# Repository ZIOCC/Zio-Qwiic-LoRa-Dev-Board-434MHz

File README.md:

# Zio Qwiic LoRa Dev Board 443MHz

> This product can be available for purchase [here](https://www.smart-prototyping.com/Zio-Qwiic-LoRa-Dev-Board-443MHz).

#### Description

We know how complicated it is to connect LoRa module, so we make your ‘connecting’ life easier. We created an Arduino IDE compatible board which combines LoRa module + ATMEGA32U4-AU. Simply use two boards, one as a transmitter and another one as a receiver, and the LoRa setup is complete!

There are two Qwiic connectors on board, so you can add more Qwiic modules within seconds without soldering and jumper wire connection. 

The Main IC ATMEGA32U4-AU has almost the same performance as ATmega328, with built-in USB so not only does it have a USB-to-Serial program and debug capability built in with no need for an FTDI-like chip, it can also act like a mouse, keyboard, USB MIDI device, etc.
You can download the driver for ATMEGA32U4-AU [here](https://github.com/adafruit/Adafruit_Windows_Drivers/releases/download/1.2/adafruit_drivers.exe). Alternatively, you can check out the installation guide [here](https://learn.adafruit.com/adafruit-arduino-ide-setup/windows-driver-installation).

The LoRa module on board is based on SX1278 and works on a 433MHz frequency. It can work as master model or slave model. With a spring antenna, the communication distance can reach up to 10 KM in open field. It is a perfect solution for building projects that need to cross a big area. We offer two kinds of LoRa modules on board (optional), the Ra-01 with spring antenna and Ra-02 with IPX antenna. 

The onboard antenna is good enough for you to test function, if you need to implement it for real projects, please solder the antenna to get the best spreading distance.

> If you are looking for the Lora Module instead, you can find it [here](https://www.smart-prototyping.com/index.php?route=product/search&search=lora)

#### Specification

* Program Memory Size (KB): 32
* CPU Speed (MIPS/DMIPS): 16
* SRAM Bytes: 2,560
* Data EEPROM/HEF (bytes): 1024
* Wireless Standard: 433MHz
* Frequency range: 420 - 450MHz

#### Links

* [PCB source file and Gerber file](https://github.com/ZIOCC/Zio-Qwiic-LoRa-Dev-Board-434MHz)
* [Demo code](https://github.com/ZIOCC/Zio-Qwiic-LoRa-Dev-Board-434MHz/tree/master/arduino-LoRa-master)
* [ATMEGA32U4-AU datasheet](http://ww1.microchip.com/downloads/en/DeviceDoc/Atmel-7766-8-bit-AVR-ATmega16U4-32U4_Datasheet.pdf)
* [Arduino IDE Bootloader](https://github.com/adafruit/Adafruit_Windows_Drivers/releases/download/1.2/adafruit_drivers.exe)

###### About Zio
> Zio is a new line of open sourced, compact, and grid layout boards, fully integrated for Arduino and Qwiic ecosystem. Designed ideally for wearables, robotics, small-space limitations or other on the go projects. Check out other awesome Zio products [here](https://www.smart-prototyping.com/Zio).

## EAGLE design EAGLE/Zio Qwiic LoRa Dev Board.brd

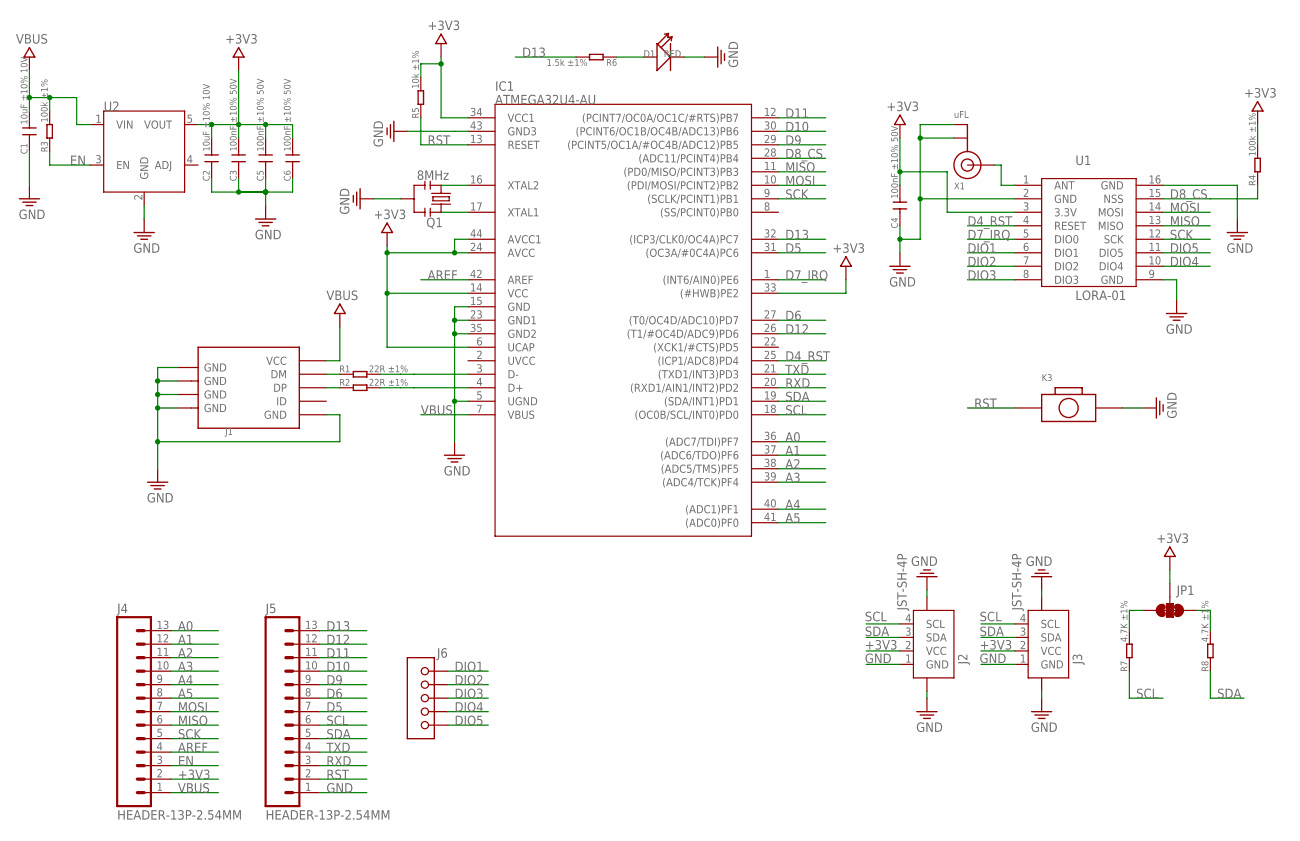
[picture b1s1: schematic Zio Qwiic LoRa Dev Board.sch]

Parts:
C1, C2: 10uF ±10% 10V; C0603
C3, C4, C5, C6: 100nF ±10% 50V; C0603
D1: RED; LED-0603
IC1: ATMEGA32U4-AU; TQFP44
J1: USB-MICROE; MICRO-SMD
J2, J3: JST-SH-4P; JST-SH-4P-90
J4, J5: HEADER-13P-2.54MM; 13P-SCREW-2.54
J6: HEADER-5P-2.54; 5P-2.54
JP1: SMT-JUMPER_3_2-NC_TRACE
K3: BOTTON-2PSKRKAEE020; SKRKAEE020
Q1: 8MHz; RESONATOR-SMD
R1, R2: 22R ±1%; R0603
R3, R4: 100k ±1%; R0603
R5: 10k ±1%; R0603
R6: 1.5k ±1%; R0603
R7, R8: 4.7K ±1%; R0603
U1: LORA-01
U2: AP2112; SOT23-5
X1: uFL; U.FL

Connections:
+3V3: C2.2, C3.2, C4.2, C5.2, C6.2, IC1.6 (UCAP), IC1.14 (VCC), IC1.24 (AVCC), IC1.33 ((#HWB)PE2), IC1.34 (VCC1), IC1.44 (AVCC1), J2.2 (VCC), J3.2 (VCC), J4.2, JP1.2, R4.2, R5.2, U1.3 (3.3V), U2.5 (VOUT)
A0: IC1.36 ((ADC7/TDI)PF7), J4.13
A1: IC1.37 ((ADC6/TDO)PF6), J4.12
A2: IC1.38 ((ADC5/TMS)PF5), J4.11
A3: IC1.39 ((ADC4/TCK)PF4), J4.10
A4: IC1.40 ((ADC1)PF1), J4.9
A5: IC1.41 ((ADC0)PF0), J4.8
AREF: IC1.42 (AREF), J4.4
D4_RST: IC1.25 ((ICP1/ADC8)PD4), U1.4 (RESET)
D5: IC1.31 ((OC3A/#0C4A)PC6), J5.7
D6: IC1.27 ((T0/OC4D/ADC10)PD7), J5.8
D7_IRQ: IC1.1 ((INT6/AIN0)PE6), U1.5 (DIO0)
D8_CS: IC1.28 ((ADC11/PCINT4)PB4), R4.1, U1.15 (NSS)
D9: IC1.29 ((PCINT5/OC1A/#OC4B/ADC12)PB5), J5.9
D10: IC1.30 ((PCINT6/OC1B/OC4B/ADC13)PB6), J5.10
D11: IC1.12 ((PCINT7/OC0A/OC1C/#RTS)PB7), J5.11
D12: IC1.26 ((T1/#OC4D/ADC9)PD6), J5.12
D13: IC1.32 ((ICP3/CLK0/OC4A)PC7), J5.13, R6.2
DIO1: J6.1, U1.6 (DIO1)
DIO2: J6.2, U1.7 (DIO2)
DIO3: J6.3, U1.8 (DIO3)
DIO4: J6.4, U1.10 (DIO4)
DIO5: J6.5, U1.11 (DIO5)
EN: J4.3, R3.1, U2.3 (EN)
GND: C1.1, C2.1, C3.1, C4.1, C5.1, C6.1, D1.-, IC1.5 (UGND), IC1.15 (GND), IC1.23 (GND1), IC1.35 (GND2), IC1.43 (GND3), J1.GND, J1.S1 (GND), J1.S1@1 (GND), J1.S1@2 (GND), J1.S2 (GND), J1.S2@1 (GND), J1.S2@2 (GND), J1.S3 (GND), J1.S3@1 (GND), J1.S3@2 (GND), J1.S4 (GND), J1.S4@1 (GND), J1.S4@2 (GND), J1.S5 (GND), J1.S6 (GND), J2.1 (GND), J2.5, J2.6, J3.1 (GND), J3.5, J3.6, J5.1, K3.2, Q1.2, U1.2 (GND), U1.9 (GND), U1.16 (GND), U2.2 (GND), X1.1 (GND), X1.2 (GND)
MISO: IC1.11 ((PD0/MISO/PCINT3)PB3), J4.6, U1.13 (MISO)
MOSI: IC1.10 ((PDI/MOSI/PCINT2)PB2), J4.7, U1.14 (MOSI)
unnamed: J1.D- (DM), R1.1
unnamed: J1.D+ (DP), R2.1
unnamed: IC1.4 (D+), R2.2
unnamed: IC1.3 (D-), R1.2
unnamed: IC1.16 (XTAL2), Q1.3
unnamed: D1.+, R6.1
unnamed: IC1.17 (XTAL1), Q1.1
unnamed: U1.1 (ANT), X1.3 (SIGNAL)
unnamed: JP1.3, R7.2
unnamed: JP1.1, R8.2
RST: IC1.13 (RESET), J5.2, K3.1, R5.1
RXD: IC1.20 ((RXD1/AIN1/INT2)PD2), J5.3
SCK: IC1.9 ((SCLK/PCINT1)PB1), J4.5, U1.12 (SCK)
SCL: IC1.18 ((OC0B/SCL/INT0)PD0), J2.4 (SCL), J3.4 (SCL), J5.6, R7.1
SDA: IC1.19 ((SDA/INT1)PD1), J2.3 (SDA), J3.3 (SDA), J5.5, R8.1
TXD: IC1.21 ((TXD1/INT3)PD3), J5.4
VBUS: C1.2, IC1.7 (VBUS), J1.VBUS (VCC), J4.1, R3.2, U2.1 (VIN)

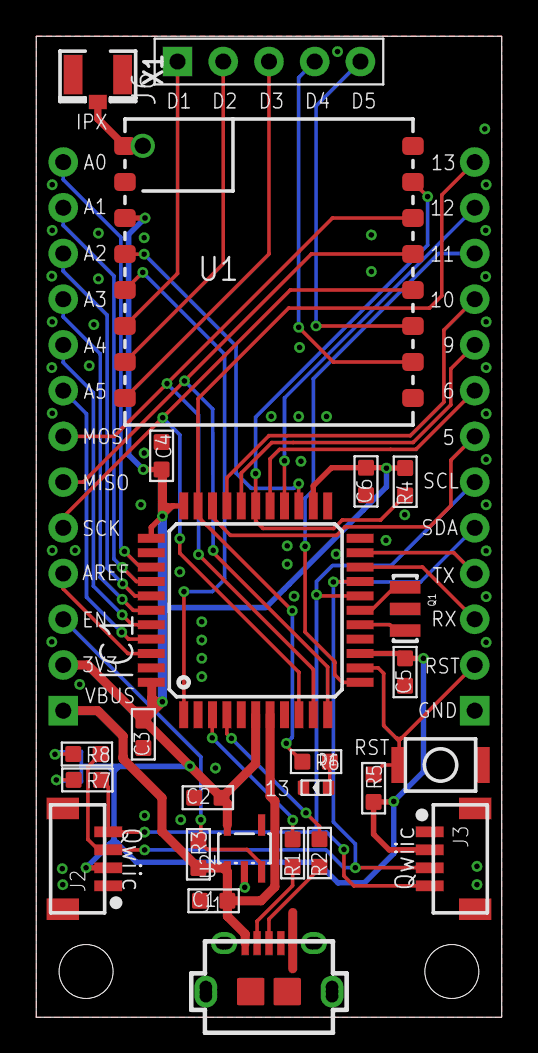
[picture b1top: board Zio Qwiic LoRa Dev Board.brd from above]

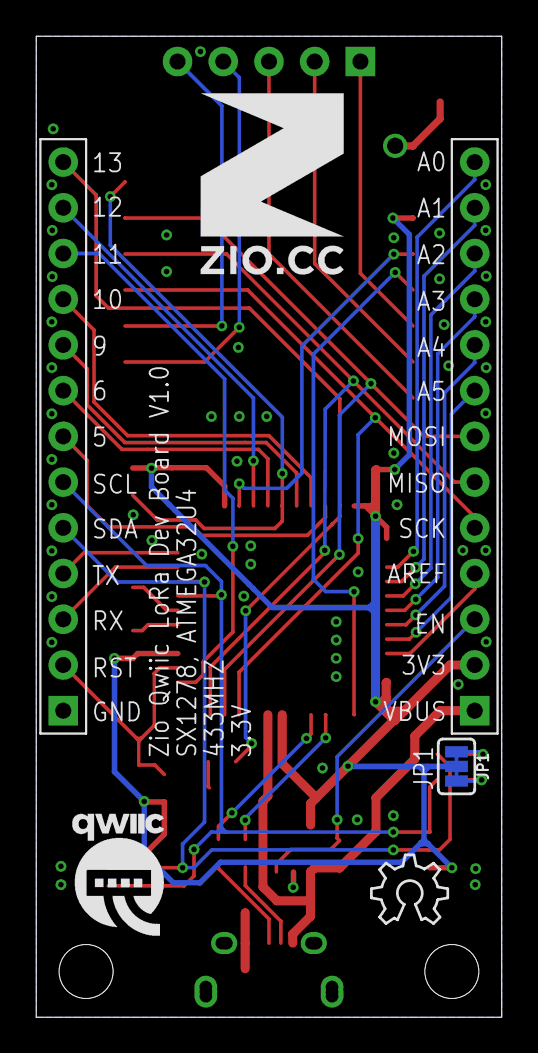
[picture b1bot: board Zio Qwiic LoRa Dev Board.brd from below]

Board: 2 copper layers, 25.9 x 54.5 mm, 31 parts (6 on the bottom side), 44 nets.

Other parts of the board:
U$10: 10MM
U$11: QWIIC-LOGO-MEDIUM
U$12: OSHW_6X150_NOTEXT

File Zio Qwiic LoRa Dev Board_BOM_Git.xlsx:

| BOM quantity |  |  | Zio Qwiic LoRa Dev Board | V 1.0 |  |  |  |  | Harry | 2018.8.31
 | Part Identification |  |  |  |  |  |  |  | Customer Information |  | Quantity
# | Part ID / Reference | Manufacturer | Part / Order Number | Description | Value | Package | THT (y/n) | Pins / Pads | Source/Link/ Datasheet/Note | Source / Target Price | Quantity per BOM
1 | C1, C2 |  |  |  | 10uF ±10% 10V | C0603 | n | 2 |  |  | 2
2 | C3, C4, C5, C6 |  |  |  | 100nF ±10% 50V | C0603 | n | 2 |  |  | 4
3 | D1 |  |  |  | RED | LED-0603 | n | 2 |  |  | 1
4 | IC1 | MICROCHIP | ATMEGA32U4-AU |  | ATMEGA32U4-AU | TQFP44 | n | 44 |  |  | 1
5 | J1 | 韩国韩荣 | U-F-M5DD-Y-L |  | U-F-M5DD-Y-L | MICRO-SMD | n | 5 |  |  | 1
6 | J2, J3 |  |  |  | JST-SH-4P | JST-SH-4P-90 | n | 6 |  |  | 2
7 | J4, J5 |  | NA |  | HEADER-13P-2.54MM | 13P-SCREW-2.54 | y | 13 |  |  | 2
8 | J6 |  | NA |  | 5P-2.54 | 5P-2.54 | y | 5 |  |  | 1
9 | K3 | ALPS | SKRKAEE020 |  | SKRKAEE020 | SKRKAEE020 | n | 2 |  |  | 1
10 | Q1 | muRata | CSTCE8M00G55-R0 |  | 8MHz | RESONATOR-SMD | n | 3 |  |  | 1
11 | R1, R2 | FH | RS-03K22R0FT |  | 22R ±1% | R0603 | n | 2 |  |  | 2
12 | R3, R4 |  |  |  | 100k ±1% | R0603 | n | 2 |  |  | 2
13 | R5 |  |  |  | 10k ±1% | R0603 | n | 2 |  |  | 1
14 | R6 | UniOhm | 0603WAF1501T5E |  | 1.5k ±1% | R0603 | n | 2 |  |  | 1
15 | R7, R8 |  |  |  | 4.7K ±1% | R0603 | n | 2 |  |  | 2
16 | U1 |  |  |  | LORA-01 | LORA-01 | n | 16 |  |  | 1
17 | U2 | DIODES | AP2112K-3.3TRG1 |  | AP2112K-3.3TRG1 | SOT23-5 | n | 5 |  |  | 1
18 | X1 |  | NA |  | uFL | U.FL | n | 3 |  |  | 1

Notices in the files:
parts and their libraries:
microbuilder: This work is placed in the public domain, and may be freely used for commercial and non-commercial work with the following conditions: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
